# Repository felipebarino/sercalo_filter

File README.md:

Excelente\! Fico feliz em saber que a correção funcionou bem. O código está muito mais robusto agora.

Com base na sua versão `1.0.0` do `main.c`, reescrevi o `README.md` para refletir com precisão todas as funcionalidades e comandos atuais. Ele está mais claro e agora inclui os comandos de energia que você adicionou.

Aqui está a versão atualizada:

-----

# Controle do Filtro Óptico Sintonizável Sercalo TF1 via ESP32

Este projeto implementa um firmware para o microcontrolador ESP32 para controlar um Filtro Óptico Sintonizável Sercalo TF1. A comunicação com os filtros (Banda C e Banda L) é feita via I2C.

A aplicação principal de exemplo estabelece uma interface de controle via porta serial (UART), permitindo que um usuário ou um programa envie comandos para consultar o estado dos filtros, definir comprimentos de onda específicos ou iniciar varreduras de espectro contínuas.

## Funcionalidades

  * **Driver I2C Dedicado:** Um componente (`sercalo_i2c_driver`) encapsula a comunicação e os comandos do protocolo I2C do filtro Sercalo TF1, de acordo com o manual do fabricante, incluindo cálculo de CRC-8 para garantir a integridade dos dados.
  * **Arquitetura Baseada em FreeRTOS:** A aplicação utiliza o FreeRTOS para gerenciar tarefas de comunicação e controle, permitindo uma operação não bloqueante e facilmente expansível.
  * **Sistema de Comandos Escalável:** A lógica de processamento de comandos utiliza uma tabela de despacho (*dispatch table*), tornando a adição de novos comandos simples e organizada, sem a necessidade de alterar o fluxo principal.
  * **Controle Robusto via Serial:** Comandos para identificar os filtros, definir comprimentos de onda, obter o estado atual e iniciar varreduras foram implementados. O protocolo é similar ao SCPI, facilitando a automação.
  * **Gerenciamento Automático de Energia:** O firmware garante que os filtros sejam ativados (retirados do modo de repouso) automaticamente antes de executar comandos de operação, aumentando a confiabilidade do sistema.

## Hardware Necessário

  * Placa de desenvolvimento ESP32.
  * Filtro Óptico Sintonizável Sercalo TF1 (Banda C e/ou L).
  * Conexões I2C entre o ESP32 e os filtros (SDA, SCL).
      * No projeto, os pinos estão configurados como:
          * **SCL:** GPIO 22
          * **SDA:** GPIO 21
  * Fonte de alimentação para o ESP32 e para os filtros Sercalo.
  * Cabo USB para programação do ESP32 e para monitoramento/controle via terminal serial.

## Estrutura do Projeto

```text
sercalo_filter/
├── main/
│   ├── CMakeLists.txt
│   └── main.c                  # Lógica principal, tasks e handlers de comando
├── components/
│   └── sercalo_i2c_driver/
│       ├── CMakeLists.txt
│       ├── include/
│       │   └── sercalo_i2c.h   # Interface pública do driver
│       └── sercalo_i2c.c       # Implementação do driver I2C
├── CMakeLists.txt              # CMake principal do projeto
├── sdkconfig                   # Configuração do projeto ESP-IDF
└── README.md                   # Este arquivo
```

## Como Compilar e Gravar

1.  **Configure o Ambiente ESP-IDF:** Certifique-se de que o ESP-IDF está instalado e que as variáveis de ambiente foram exportadas (`. export.sh` ou `get_idf`).

2.  **Configure o Projeto:**

      * Defina o target do ESP32: `idf.py set-target esp32`.
      * Ajuste as configurações do projeto, se necessário, com `idf.py menuconfig`.
          * Verifique se as configurações de GPIO para I2C em `main/main.c` correspondem ao seu hardware.

3.  **Compile o Projeto:**

    ```bash
    idf.py build
    ```

4.  **Grave o Firmware no ESP32:**

      * Conecte o ESP32 ao computador.
      * Execute o comando abaixo, substituindo `/dev/ttyUSB0` pela porta serial correta.
        ```bash
        idf.py -p /dev/ttyUSB0 flash monitor
        ```
      * O comando `monitor` abrirá o terminal serial para interagir com o dispositivo.

## Protocolo de Comunicação

Todos os comandos são enviados via UART e devem seguir um formato específico.

1.  **Início do Comando:** Todo comando deve começar com o caractere dois-pontos (`:`).
2.  **Corpo do Comando:** Segue o nome do comando e seus argumentos, separados por `?` ou `:`.
3.  **Fim do Comando:** O comando é finalizado com um caractere de nova linha (`\n` ou `\r`).

**Formato Geral:**

```
:comando[?|:][argumentos]\n
```

### Formato das Respostas

  * **Sucesso:** A resposta começa com `:ACK`, opcionalmente seguida por dados.
    ```
    :ACK
    :ACK:[dados da resposta]
    ```
  * **Erro:** A resposta começa com `:NACK`, seguida por uma mensagem que descreve o erro.
    ```
    :NACK:[mensagem de erro]
    ```

-----

## Referência de Comandos

### `iden`

Recupera as informações de identificação de ambos os filtros (Banda C e Banda L).

  * **Descrição:** Solicita modelo, número de série (S/N) e versão de firmware de cada canal.
  * **Sintaxe:**
    ```
    :iden\n
    ```
  * **Exemplo de Resposta:**
    ```
    :ACK: Canal C: Modelo=TF, S/N=N/A, FW=7.0 | Canal L: Modelo=TF, S/N=N/A, FW=6.0 | 
    ```

### `get-interval`

Obtém o intervalo operacional (comprimentos de onda mínimo e máximo) de um filtro específico.

  * **Sintaxe:**
    ```
    :get-interval?[banda]\n
    ```
  * **Argumentos:**
      * `banda`: O canal do filtro (`C` ou `L`).
  * **Exemplo de Uso:**
      * **Comando:** `:get-interval?C\n`
      * **Resposta:** `:ACK:(1527.608,1565.503)`

### `get-wl`

Obtém o comprimento de onda (`wavelength`) atual de um filtro específico.

  * **Sintaxe:**
    ```
    :get-wl?[banda]\n
    ```
  * **Argumentos:**
      * `banda`: O canal do filtro (`C` ou `L`).
  * **Exemplo de Uso:**
      * **Comando:** `:get-wl?L\n`
      * **Resposta:** `:ACK:1575.500`

### `set-wl`

Define um novo comprimento de onda para um filtro específico.

  * **Descrição:** Sintoniza o canal para um novo comprimento de onda. Se uma varredura (`sweep`) estiver ativa, ela será interrompida.
  * **Sintaxe:**
    ```
    :set-wl:[banda]:[wavelength]\n
    ```
  * **Argumentos:**
      * `banda`: O canal do filtro a ser sintonizado (`C` ou `L`).
      * `wavelength`: O comprimento de onda desejado em nanômetros (nm).
  * **Exemplo de Uso:**
      * **Comando:** `:set-wl:C:1550.5\n`
      * **Resposta:** `:ACK`

### `sweep`

Inicia uma varredura contínua de comprimento de onda para um filtro. ⚙️

  * **Descrição:** Inicia uma tarefa que varre uma faixa de comprimentos de onda em intervalos de tempo definidos. A varredura reinicia automaticamente ao chegar ao fim. Se uma varredura já estiver ativa no canal, ela será substituída.
  * **Sintaxe:**
    ```
    :sweep:[banda]:[min_wl]:[max_wl]:[passo_wl]:[passo_tempo_ms]\n
    ```
  * **Argumentos:**
      * `banda`: O canal do filtro (`C` ou `L`).
      * `min_wl`: Comprimento de onda inicial (nm).
      * `max_wl`: Comprimento de onda final (nm).
      * `passo_wl`: Incremento do comprimento de onda a cada passo (nm).
      * `passo_tempo_ms`: Intervalo de tempo entre cada passo (milissegundos).
  * **Exemplo de Uso:**
      * **Comando:** `:sweep:L:1570:1605:0.5:1000\n`
      * **Resposta:** `:ACK`

### `powerup`

Força a ativação (modo de energia normal) de ambos os filtros.

  * **Descrição:** Garante que ambos os canais estejam prontos para receber comandos de operação.
  * **Sintaxe:**
    ```
    :powerup\n
    ```
  * **Exemplo de Resposta:**
    ```
    :ACK:Canal C: Ligado | Canal L: Ligado | 
    ```

### `get-power`

Verifica o estado de energia atual de ambos os filtros.

  * **Descrição:** Retorna `1` para modo normal (ligado) e `0` para modo de baixo consumo (repouso).
  * **Sintaxe:**
    ```
    :get-power\n
    ```
  * **Exemplo de Resposta:**
    ```
    :ACK:Canal C: 1 | Canal L: 1 | 
    ```

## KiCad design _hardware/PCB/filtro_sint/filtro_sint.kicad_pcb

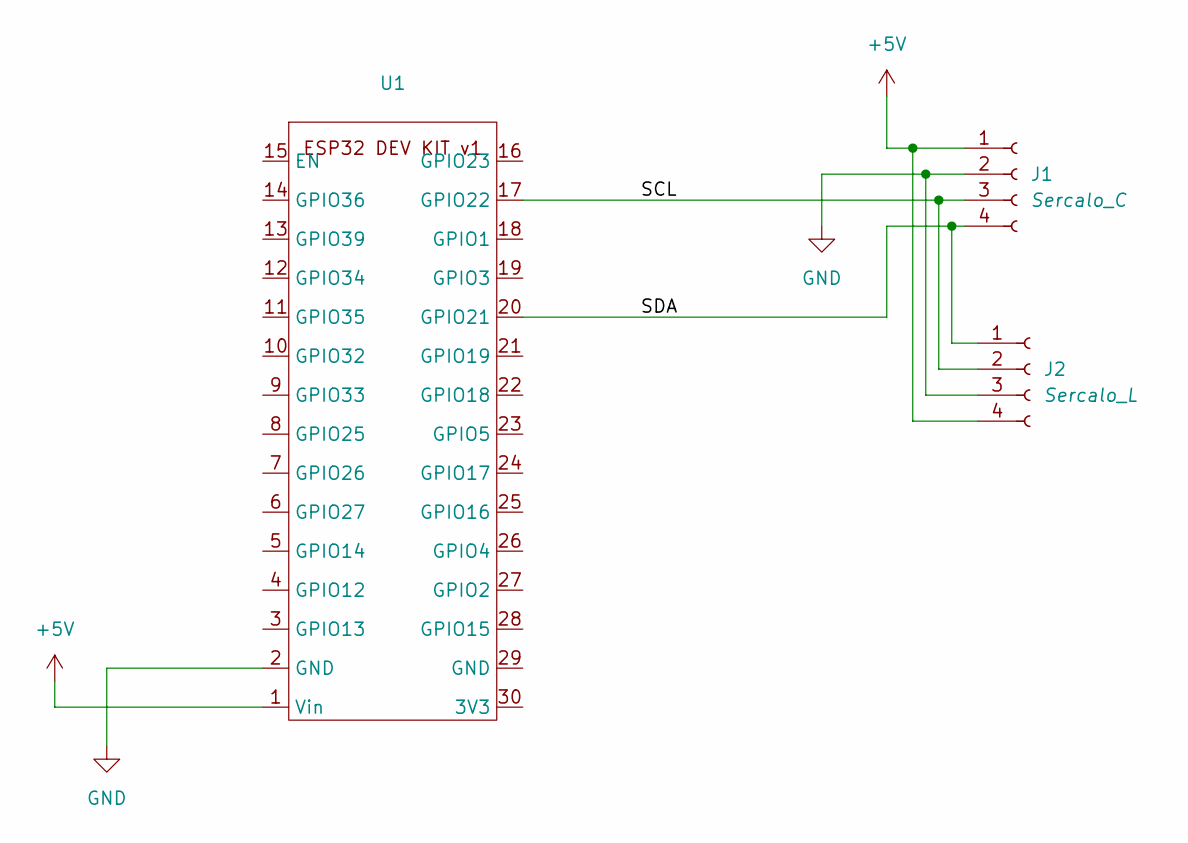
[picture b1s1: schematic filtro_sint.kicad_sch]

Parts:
J1: Sercalo_C; Molex_KK-254_AE-6410-04A_1x04_P2.54mm_Vertical
J2: Sercalo_L; Molex_KK-254_AE-6410-04A_1x04_P2.54mm_Vertical
U1: esp32_devkitv1_doit

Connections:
+5V: J1.1, J2.4, U1.1 (Vin)
/SCL: J1.3, J2.2, U1.17 (GPIO22)
/SDA: J1.4, J2.1, U1.20 (GPIO21)
GND: J1.2, J2.3, U1.2 (GND)

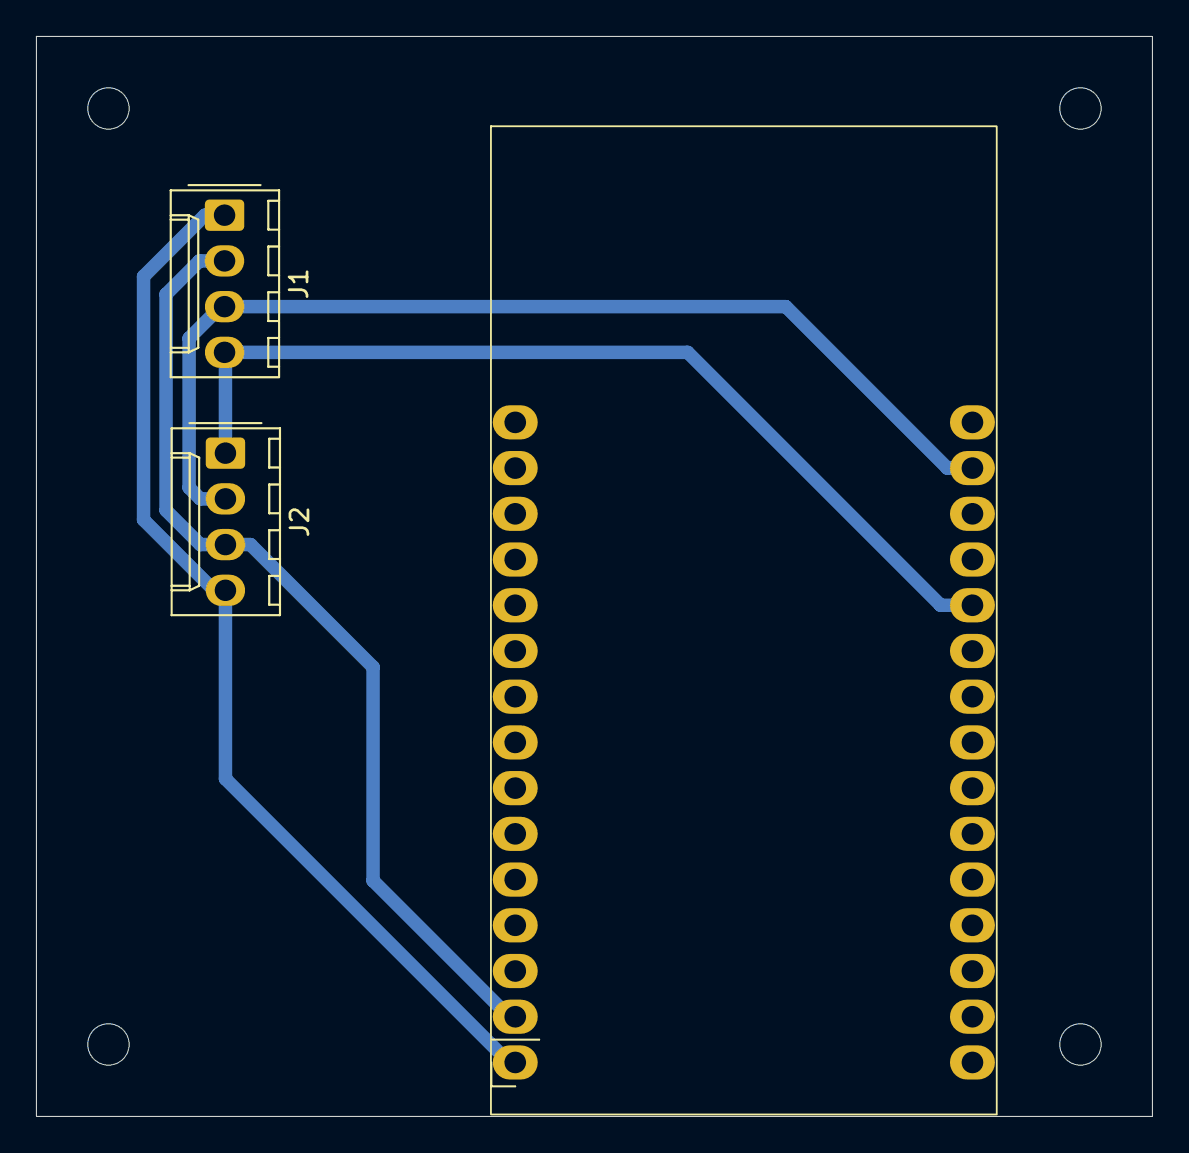
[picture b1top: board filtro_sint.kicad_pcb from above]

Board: 2 copper layers, 62.0 x 60.0 mm, 3 parts (0 on the bottom side), 4 nets.

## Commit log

2025-07-18 init
2025-07-18 interface de controle
2025-07-22 atualiza main
